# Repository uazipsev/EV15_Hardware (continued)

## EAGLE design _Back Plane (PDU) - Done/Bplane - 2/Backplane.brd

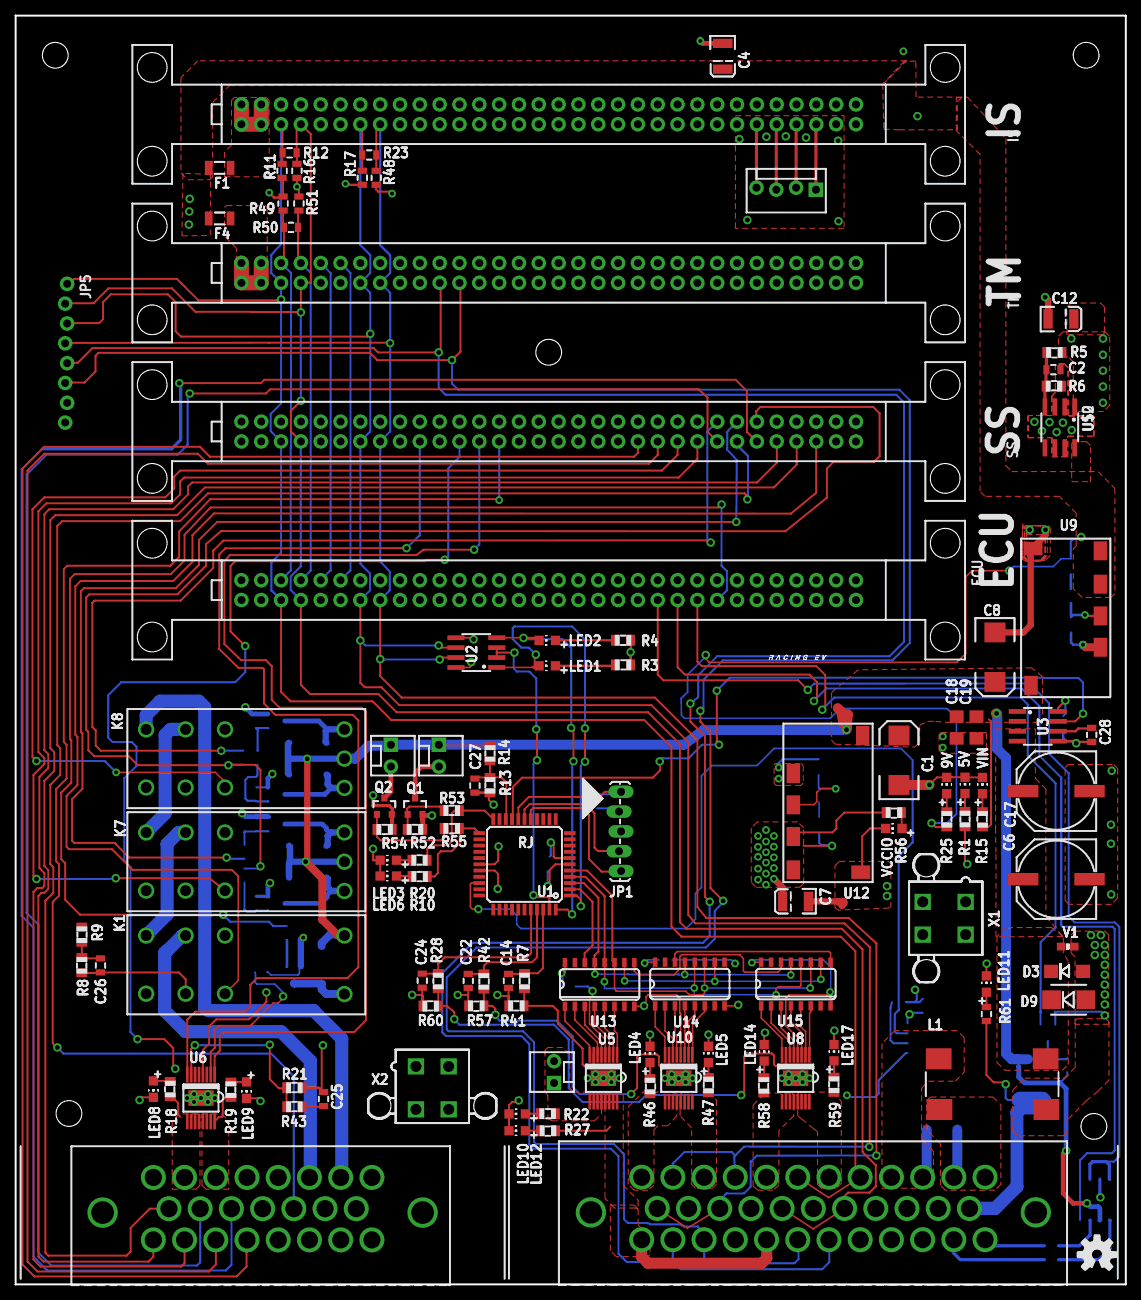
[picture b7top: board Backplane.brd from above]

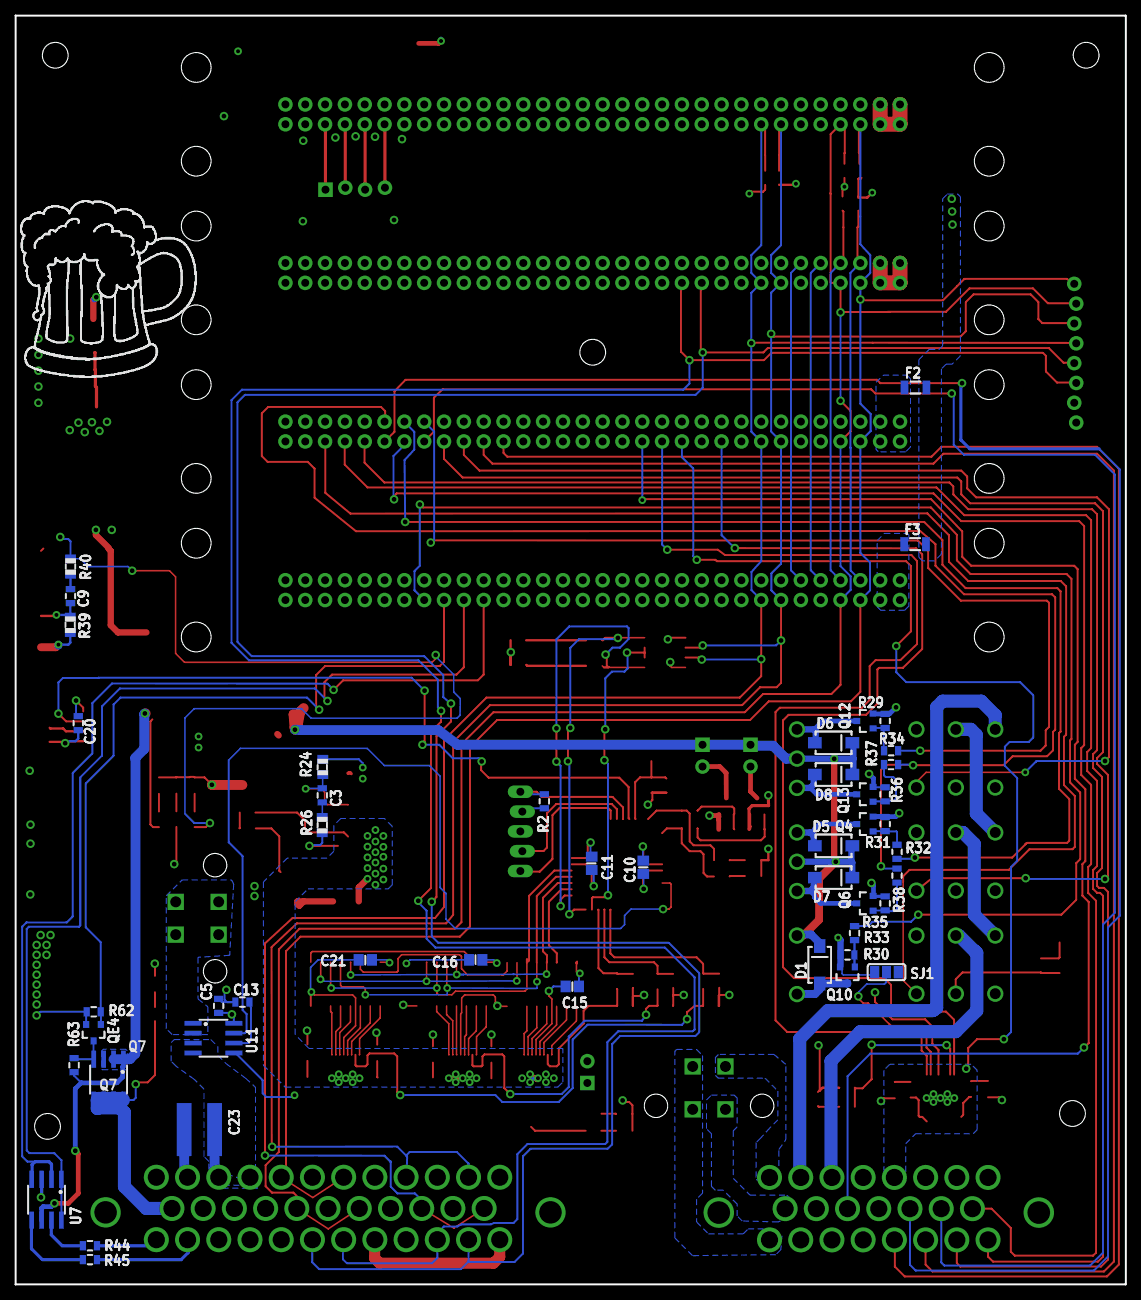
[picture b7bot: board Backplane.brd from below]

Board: 4 copper layers, 142.2 x 162.6 mm, 172 parts (48 on the bottom side), 153 nets.

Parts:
5V, 9V: Green; CHIP-LED0805
C1, C8: 10uF; EIA7343
C2, C5, C13, C20: 0.1uF; 0805
C3: DNP; 0805
C4, C7, C12: 10uF; EIA3528
C6, C17: 100uF; PANASONIC_G
C9: dnp; 0805
C10, C11, C15, C16, C21: .1uF; C0805
C14, C22, C24, C25: 10nF; 0805
C18, C19: 1uf; 1206
C23: 1000pf; C1825
C26, C27: 1uF; 0805
C28: .1uF; 0805
D1, D5, D6, D7, D8: ES1AE-TP; SMA-DIODE-KIT
D3: TVS; DO-214AC
D9: 30V; SMB-DIODE
F1, F2, F3, F4: PTCSMD; PTC-1206
J1: M23; 1-770669-1
J2: M35; 1-776163-2
JP1: 1X05_LOCK_LONGPADS
JP2, JP3, JP4: M02POLAR_LOCK; MOLEX-1X2_LOCK
JP5: 1X08_LOCK_NO_SILK
JP7: Headphone; MOLEX-1X4_LOCK
K1: RTE44024F
K7, K8: RT424F24
L1: ACM1513-551-2PL-TL
LED1, LED4, LED5, LED6, LED8, LED9, LED10, LED12, LED14, LED17: green; CHIP-LED0805
LED2, LED3: red; CHIP-LED0805
LED11: CHIP-LED0805
Q1, Q2, Q4, Q6, Q10, Q12, Q13: BSS123; SOT23-3
Q7: Si9435BDY; SO08
QE4: BSS123; SOT-23
R1, R3, R4, R5, R6, R7, R10, R18, R19, R20, R21, R22, R27, R28, R41, R42, R43, R46, R47, R53, R55, R57, R58, R59, R60: 1k; R0805
R2, R29, R30, R31, R35, R36, R62: 10k; 0805
R8, R13: 24k; R0805
R9, R14: 91k; R0805
R11, R16, R17, R48, R49, R51: 523; 0805
R12, R23, R50: 120; 0805
R15, R25, R56: 1.21k; R0805
R24, R39: 8.43k; R0805
R26, R40: dnp; R0805
R32, R33, R34, R37, R38: 1k; 0805
R44, R45: 0; 0805
R52, R54: 100k; R0805
R61: 2.2k; 0805
R63: 22k; 0805
SJ1: PAD-JUMPER-3-NO_YES_SILK_FULL_BOX
STANDOFF1, STANDOFF2, STANDOFF3, STANDOFF4, STANDOFF5: STAND-OFF
U1: PIC18F45K22; TQFP-44
U2: SN75HVD08DR; SO-8
U3, U11: ACS712; SO-8
U5, U6, U8, U10: VND7040AJTR-E; SSO-16-POWER
U7: FAN3278TMX; SO-8
U9, U12: APXW005A0X43-SRZ
U13, U14, U15: 74LS595D; SO16
U$1, U$4, U$5, U$6: CARD-SLOT; CS64
U$2: LM2931; SO08
U$3: BEERL; B-L
U$7: LOGO; L-MS
U$8: OSHW-LOGOM; OSHW-LOGO-M
U$9: INDPK1; PICKIT-PIN-1
V1: 30V; 0603-RES
VCCIO: Green; CHIP-LED0805
VIN: Green; CHIP-LED0805
X1, X2: 5566-4

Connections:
1AVAL: C22.1, R42.1, U1.41
2AVAL: C24.1, R28.1, U1.40
3AVAL: C14.1, R7.1, U1.42
+5V: C5.1, C10.1, C11.1, C12.A, C15.1, C16.1, C20.1, C21.1, JP1.2, R1.2, R2.2, R3.2, R4.2, R5.2, R11.2, R17.2, R49.2, U1.7, U1.28, U2.8, U3.8, U11.8, U13.16, U14.16, U15.16, U$2.1
+9V: C4.A, F1.2, F2.2, F3.2, F4.2, R25.2, R40.1, U9.5, U9.6, U$2.8
+24V: C1.A, C8.A, C18.1, C19.1, D1.C, D5.C, D6.C, D7.C, D8.C, JP3.1, JP4.1, K1.A1, K7.A3, K8.A3, Q7.1, Q7.2, Q7.3, R14.2, R15.2, R63.2, U3.1, U3.2, U7.6, U9.2, U12.2
AIR-BOT+PRE: J1.3, R19.2, U6.13, U6.14, U6.15, U6.16
AIR-P: J1.8, X2.1
AIR-TOP: J1.2, R18.2, U6.9, U6.10, U6.11, U6.12
AMD-SEN: J1.17, U$6.28
B-LIGHT: J2.23, Q7.5, Q7.6, Q7.7, Q7.8, R61.2
B-LIGHT-C: QE4.1, R62.2, U$1.24
BMS-P: J2.1, R46.2, U10.9, U10.10, U10.11, U10.12
BOTS-SEN: J1.16, U$6.29
BPD-R-SET: R34.2, U$6.57
BPD-SEN: K8.22, U$6.23
CLEAR: U13.10, U14.10, U15.10
CLK: U1.5, U13.11, U14.11, U15.11
CSENSE: U1.19, U3.7
DATA-IN: U1.2, U13.14
DDS-P: J2.7, R59.2, U8.13, U8.14, U8.15, U8.16
ECU-RELAY: R33.2, U$1.25
ECU-SEN: K1.22, U$6.30
FAN: J1.15, X2.3
FROM-TSMS: J1.4, U6.EP, U$6.12
GND: 5V.C, 9V.C, C1.C, C2.2, C4.C, C5.2, C6.-, C7.C, C8.C, C10.2, C11.2, C12.C, C13.2, C14.2, C15.2, C16.2, C17.-, C18.2, C19.2, C20.2, C21.2, C22.2, C24.2, C25.2, C26.2, C27.2, C28.2, D3.A, D9.A, J2.14, J2.16, J2.18, J2.20, J2.22, J2.27, J2.31, JP1.3, JP5.7, JP5.8, K1.21, K7.21, K8.21, L1.OUT-, LED3.C, LED4.C, LED5.C, LED6.C, LED8.C, LED9.C, LED10.C, LED11.C, LED12.C, LED14.C, LED17.C, Q1.2, Q2.2, Q4.2, Q6.2, Q10.2, Q12.2, Q13.2, QE4.2, R6.1, R8.1, R13.1, R16.1, R21.2, R24.2, R29.1, R30.1, R31.1, R35.1, R36.1, R39.2, R41.2, R48.1, R51.1, R52.1, R54.1, R57.2, R60.2, R62.1, SJ1.3, U1.6, U1.29, U2.5, U3.5, U5.4, U6.4, U7.3, U8.4, U9.1, U9.3, U10.4, U11.5, U12.1, U12.3, U13.8, U14.8, U15.8, U$1.31, U$1.32, U$1.63, U$1.64, U$2.2, U$2.3, U$2.6, U$2.7, U$4.31, U$4.32, U$4.63, U$4.64, U$5.31, U$5.32, U$5.63, U$5.64, U$6.31, U$6.32, U$6.63, U$6.64, V1.1, VCCIO.C, VIN.C
H-EN: U7.1, U7.8, U$1.23
H-SIG: U7.2, U7.4, U$1.22
HCMESURE: U1.31, U11.7
HORN+: J2.35, R44.2
HORN-: J2.34, R45.2
IMD-INPUT: J1.13, U$6.14
IMD-R-SET: R32.2, U$6.58
IMD-SEN: K7.22, U$6.24
IS-SEN: J1.18, U$6.22
LAT: U1.4, U13.12, U14.12, U15.12
LED1: R20.2, R53.2, U1.22
LED2: R10.2, R55.2, U1.23
LOOP-IN: J1.6, K1.11
MAIN: U6.8, U$6.10
MCS-P: J2.3, R47.2, U10.13, U10.14, U10.15, U10.16
unnamed: R56.1, VCCIO.A
unnamed: LED8.A, R18.1
unnamed: C2.1, R5.1, R6.2, U$2.4
unnamed: U10.8, U14.1
unnamed: F1.1, U$5.1, U$5.2, U$5.33, U$5.34
unnamed: Q4.1, R31.2, R32.1
unnamed: K1.14, K7.11
unnamed: 9V.A, R25.1
unnamed: F2.1, U$6.1, U$6.2, U$6.33, U$6.34
unnamed: LED9.A, R19.1
unnamed: R21.1, R43.2, U6.7
unnamed: F3.1, U$1.1, U$1.2, U$1.33, U$1.34
unnamed: F4.1, U$4.1, U$4.2, U$4.33, U$4.34
unnamed: SJ1.2, U6.2
unnamed: K7.14, K8.11
unnamed: LED3.A, R20.1
unnamed: JP2.1, JP2.2, R22.2, U5.9, U5.10, U5.11, U5.12
unnamed: C28.1, U3.6
unnamed: 5V.A, R1.1
unnamed: JP7.1, U$5.30
unnamed: JP3.2, Q1.3
unnamed: JP4.2, Q2.3
unnamed: Q6.1, R35.2, R38.2
unnamed: LED1.A, R3.1
unnamed: LED2.A, R4.1
unnamed: Q1.1, R52.2, R53.1
unnamed: Q2.1, R54.2, R55.1
unnamed: LED10.A, R22.1
unnamed: LED12.A, R27.1
unnamed: C6.+, C17.+, D3.C, D9.C, L1.OUT+, U3.3, U3.4, V1.2
unnamed: R7.2, R41.1, U5.7
unnamed: Q7.4, QE4.3, R63.1
unnamed: U10.6, U14.2
unnamed: LED11.A, R61.1
unnamed: C3.1, R26.2
unnamed: U10.5, U14.3
unnamed: C3.2, R24.1, U12.4
unnamed: JP7.2, U$5.29
unnamed: U10.3, U14.4
unnamed: JP1.4, U1.17
unnamed: U$1.38, U$4.38
unnamed: R15.1, VIN.A
unnamed: JP1.5, U1.16
unnamed: U10.2, U14.5
unnamed: D1.A, K1.A2, Q10.3
unnamed: JP1.1, R2.1, U1.18
unnamed: D5.A, K7.A1, Q4.3
unnamed: Q10.1, R30.2, R33.1
unnamed: D7.A, K7.A2, Q6.3
unnamed: D6.A, K8.A1, Q12.3
unnamed: D8.A, K8.A2, Q13.3
unnamed: R44.1, U7.7
unnamed: R45.1, U7.5
unnamed: LED6.A, R10.1
unnamed: Q13.1, R36.2, R37.2
unnamed: JP7.3, U$5.28
unnamed: U$1.37, U$4.37
unnamed: Q12.1, R29.2, R34.1
unnamed: C9.1, R40.2
unnamed: C9.2, R39.1, U9.4
unnamed: U11.1, U11.2, X1.1, X1.2, X1.3, X1.4
unnamed: U10.1, U14.6
unnamed: C13.1, U11.6
unnamed: U8.8, U15.1
unnamed: U8.6, U15.2
unnamed: U8.5, U15.3
unnamed: LED4.A, R46.1
unnamed: LED5.A, R47.1
unnamed: R42.2, R57.1, U10.7
unnamed: U8.3, U15.4
unnamed: U8.2, U15.5
unnamed: U8.1, U15.6
unnamed: U5.8, U13.1
unnamed: U5.6, U13.2
unnamed: U5.5, U13.3
unnamed: U5.3, U13.4
unnamed: U5.2, U13.5
unnamed: U5.1, U13.6
unnamed: U13.9, U15.14
unnamed: U14.14, U15.9
unnamed: JP7.4, U$5.27
unnamed: LED14.A, R58.1
unnamed: LED17.A, R59.1
unnamed: R28.2, R60.1, U8.7
OUTEN: U1.3, U13.13, U14.13, U15.13
P+F: J1.23, X2.2
PRE+: U6.1, U$6.13
RAVAL: C25.1, R43.1
RELAY-SET: R37.1, R38.1, U$6.59
RS1-A: J2.6, J2.8, JP5.1, R11.1, R12.2, U$1.3, U$4.3, U$5.3, U$6.3
RS1-B: J2.17, J2.19, JP5.2, R12.1, R16.2, U$1.4, U$4.4, U$5.4, U$6.4
RS2-A: J2.2, J2.4, JP5.3, R17.1, R23.2, U2.6, U$1.7, U$4.7, U$5.7, U$6.7
RS2-B: J2.13, J2.15, JP5.4, R23.1, R48.2, U2.7, U$1.8, U$4.8, U$5.8, U$6.8
RS3-A: R49.1, R50.2, U$1.35, U$4.35
RS3-B: R50.1, R51.2, U$1.36, U$4.36
RX: LED1.C, U1.1, U2.1
SAS-P: J2.5, R58.2, U8.9, U8.10, U8.11, U8.12
SSW_C_SEN: J1.10, U$6.25
SSW_L-SEN: J1.11, U$6.27
SSW_R-SEN: J1.9, U$6.26
TO-TSMS: J1.7, K8.14
TSA: J2.25, J2.30, JP5.5, U$4.11
TSB: J2.26, J2.29, JP5.6, U$4.12
TSMS-SEN: J1.19, U$6.21
TSS-P: J2.24, J2.28, R27.2, U5.13, U5.14, U5.15, U5.16
TX: LED2.C, U1.44, U2.4
U2-CNT: U1.43, U2.2, U2.3
VCCIO: C7.A, R26.1, R56.2, U5.EP, U8.EP, U10.EP, U12.5, U12.6
VGND: C23.2, J2.11, J2.12, L1.IN-
VIN: C23.1, J2.9, J2.10, L1.IN+, U11.3, U11.4
VSENSE: C27.1, R13.2, R14.1, U1.20
VSENSE2: C26.1, R8.2, R9.1
